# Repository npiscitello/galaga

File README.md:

# Sample Rate
If we run the system on the 8MHz internal clock and use 8-bit resolution PWM for the audio, we'll
have a sample rate of 8000000/256=31250 Hz. I used Audacity to prepare the audio files - project
rate of 31250, split into mono and delete one channel, then export the audio to unsigned 8 bit raw.

# FAT Driver
FatFS driver - see http://elm-chan.org/fsw/ff/00index_e.html (may take a while to load)

# KiCAD
Required libraries (may not be an all-inclusive list...):
 * custom library, bundled in this repo
 * Device
 * Connector
 * MCU_Microchip_ATmega
 * Amplifier_Audio
 * Regulator_Linear

# Random Number Generator
This project needs some way to decide which sound to play. The easy way out is
to just play one sound over and over, but I wanted more variety. I could rotate
over a list of sounds sequentially, but then I'd have to store which sound
played previously in the EEPROM and worry about wear leveling and all sorts of
mess, so I decided to just choose a random sound every time the chip starts up.
This also has the added bonus of not getting locked into a monotonous loop if
you want to play a few sounds in a row.

On the advice of a few threads over at AVRFreaks, I played around with using ADC
noise as an entropy source for a random number generator. I tried using the
internal temp sensor, but it ended up working much better to use ADC5, the pin
furthest from the GND pin. It probably didn't matter which pin I used (not that
I tested pin vs. pin performance), but it seemed like that was a free way to get
a little bit more noise on the line. That's a weird sentence to type, but noise
is desirable in this case!

The random number generator itself is dead simple - I read the two LSBs of the
ADC four times to fill an 8 bit unsigned int then just modulo that number with
the number of entries in my sound file array. That number is just an index into
that array and bam - random sound. See `code/main_code/sound_files.c` for the
implementation.

To test the randomness I cycled the chip 100 times and recorded the output of
the RNG. The histogram of the results is shown below - not the most even
distribution but certainly random enough for my purposes. This test also
doubled as a stability test, and I'm happy to report that it ran flawlessly,
with no errors or hiccups, all 100 times in a row!

![Histogram showing the results of 100 test runs of the RNG. The distribution is
satisfactorily random.](code/main_code/rng_histogram.png)

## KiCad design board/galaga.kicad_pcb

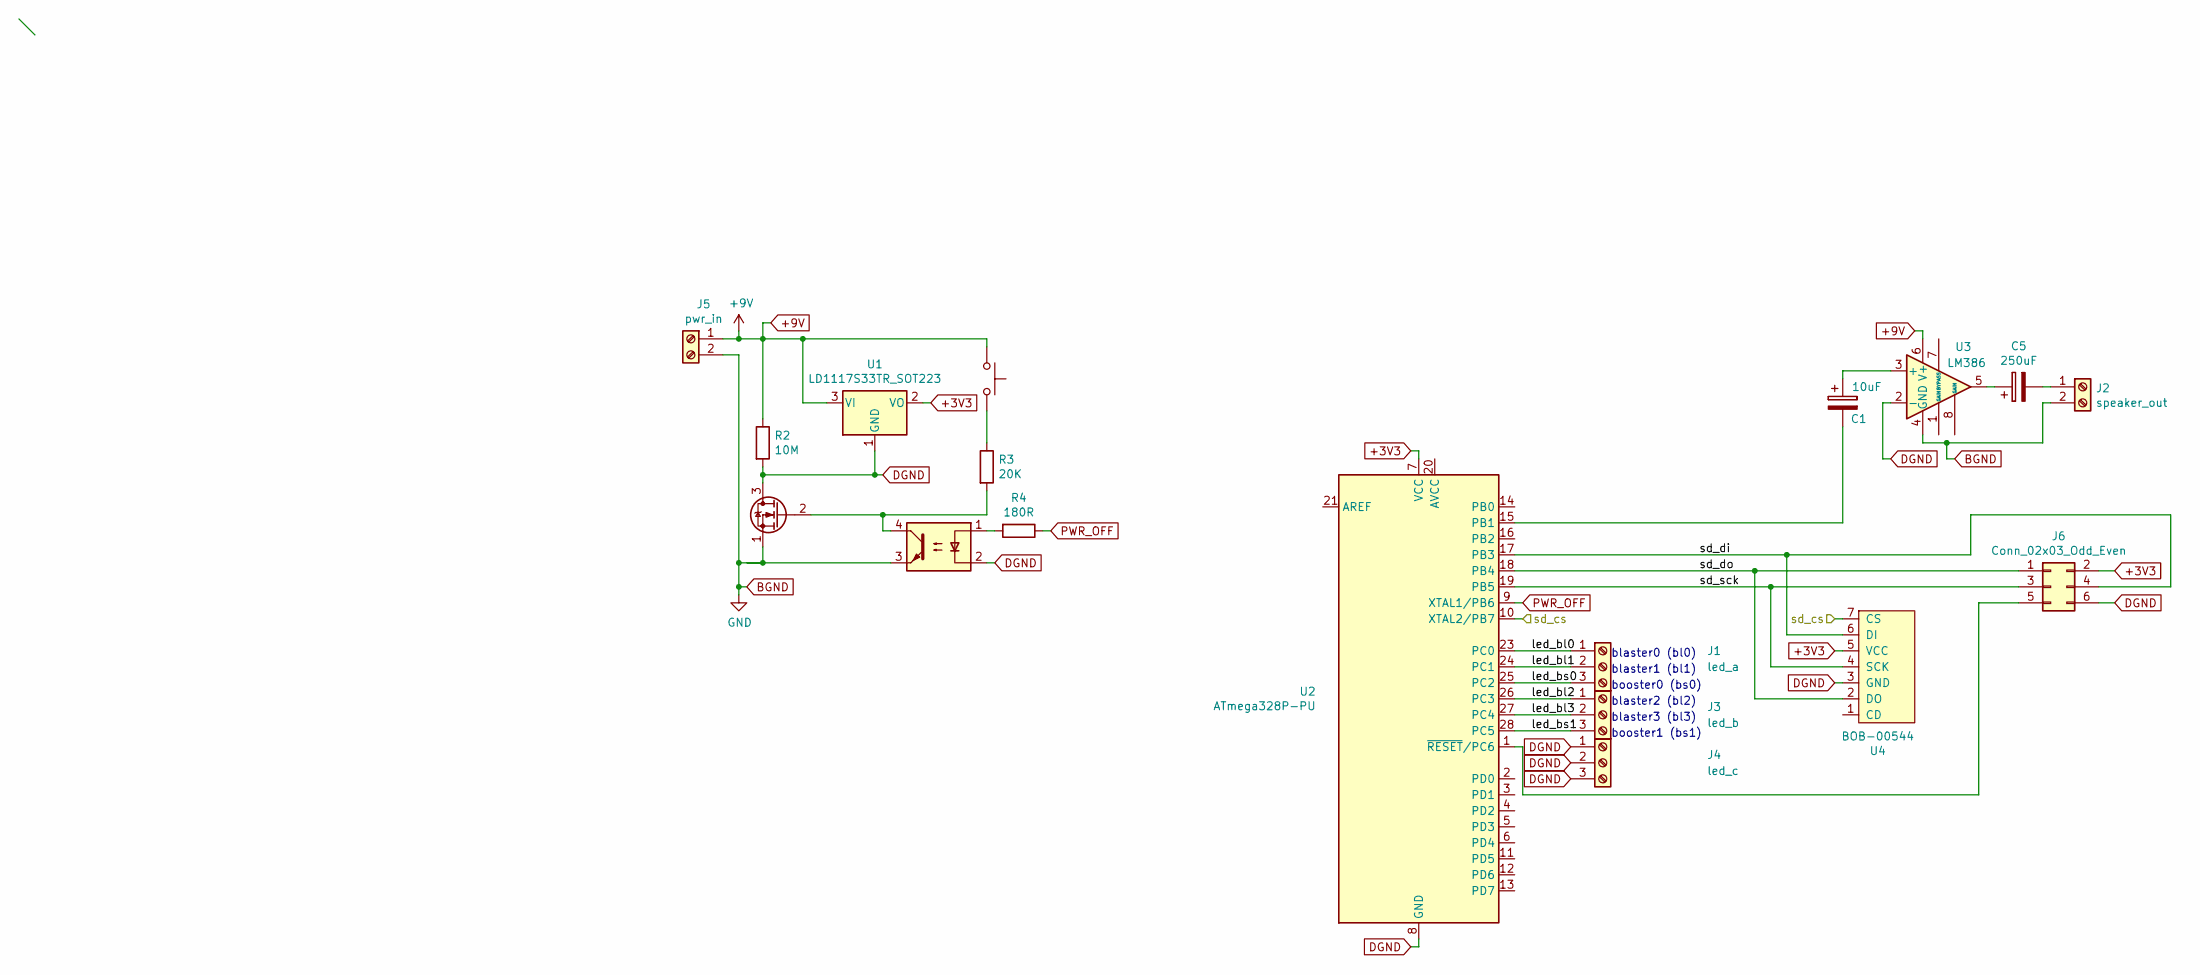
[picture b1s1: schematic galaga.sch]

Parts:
C1: 10uF; CP_Axial_L10.0mm_D6.0mm_P15.00mm_Horizontal
C5: 250uF; CP_Axial_L20.0mm_D10.0mm_P26.00mm_Horizontal
J1: led_a; TerminalBlock_TE_282834-3_1x03_P2.54mm_Horizontal
J2: speaker_out; TerminalBlock_TE_282834-2_1x02_P2.54mm_Horizontal
J3: led_b; TerminalBlock_TE_282834-3_1x03_P2.54mm_Horizontal
J4: led_c; TerminalBlock_TE_282834-3_1x03_P2.54mm_Horizontal
J5: pwr_in; TerminalBlock_TE_282834-2_1x02_P2.54mm_Horizontal
J6: Conn_02x03_Odd_Even; PinHeader_2x03_P2.54mm_Vertical
Q1: 2N7000; TO-220-3_Vertical
R2: 10M; R_Axial_DIN0207_L6.3mm_D2.5mm_P2.54mm_Vertical
R3: 20K; R_Axial_DIN0207_L6.3mm_D2.5mm_P2.54mm_Vertical
R4: 180R; R_Axial_DIN0207_L6.3mm_D2.5mm_P2.54mm_Vertical
SW1: SW_Push; TerminalBlock_TE_282834-2_1x02_P2.54mm_Horizontal
U1: LD1117S33TR_SOT223; TO-220-3_Vertical
U2: ATmega328P-PU; DIP-28_W7.62mm
U3: LM386; DIP-8_W7.62mm
U4: BOB-00544; PinHeader_1x07_P2.54mm_Vertical
U5: LTV-817M; DIP-4_W10.16mm

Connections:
+3V3: J6.2, U1.2 (VO), U2.7 (VCC), U4.5 (VCC)
+9V: J5.1, R2.1, SW1.1, U1.3 (VI), U3.6 (V+)
/led_bl0: J1.1, U2.23 (PC0)
/led_bl1: J1.2, U2.24 (PC1)
/led_bl2: J3.1, U2.26 (PC3)
/led_bl3: J3.2, U2.27 (PC4)
/led_bs0: J1.3, U2.25 (PC2)
/led_bs1: J3.3, U2.28 (PC5)
/sd_di: J6.4, U2.17 (PB3), U4.6 (DI)
/sd_do: J6.1, U2.18 (PB4), U4.2 (DO)
/sd_sck: J6.3, U2.19 (PB5), U4.4 (SCK)
BGND: J2.2, J5.2, Q1.1 (S), U3.4 (GND), U5.3
DGND: J4.1, J4.2, J4.3, J6.6, Q1.3 (D), R2.2, U1.1 (GND), U2.8 (GND), U2.22 (GND), U3.2 (-), U4.3 (GND), U5.2
unnamed: C1.1, U3.3 (+)
unnamed: C1.2, U2.15 (PB1)
unnamed: C5.1, U3.5
unnamed: C5.2, J2.1
unnamed: J6.5, U2.1 (~RESET~/PC6)
unnamed: Q1.2 (G), R3.2, U5.4
unnamed: R3.1, SW1.2
unnamed: R4.2, U5.1
PWR_OFF: R4.1, U2.9 (XTAL1/PB6)

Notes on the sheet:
blaster0 (bl0)
blaster1 (bl1)
blaster2 (bl2)
blaster3 (bl3)
booster0 (bs0)
booster1 (bs1)

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
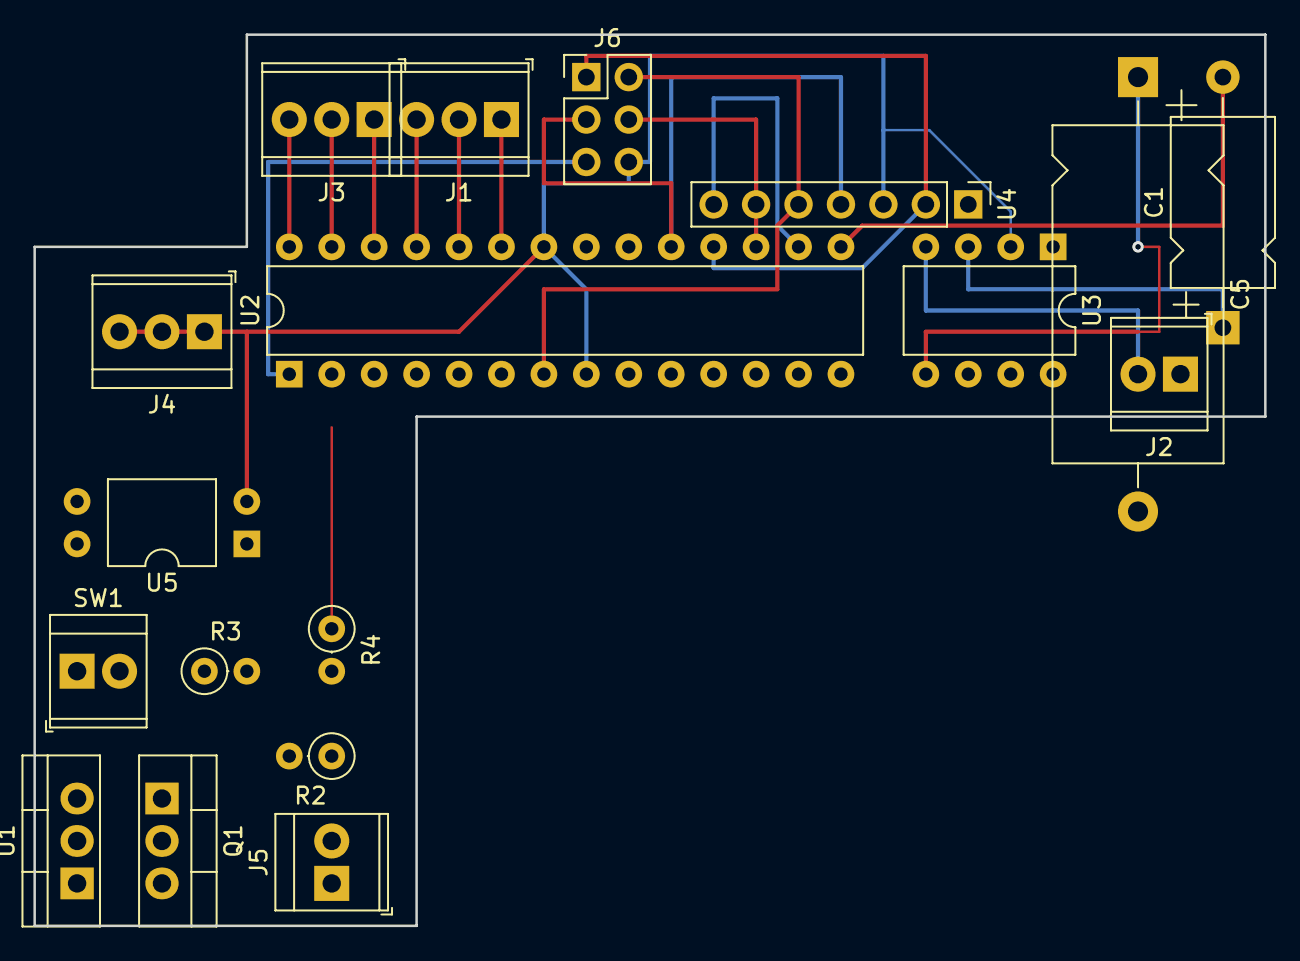
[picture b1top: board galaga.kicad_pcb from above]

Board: 2 copper layers, 73.7 x 53.3 mm, 18 parts (0 on the bottom side), 23 nets.

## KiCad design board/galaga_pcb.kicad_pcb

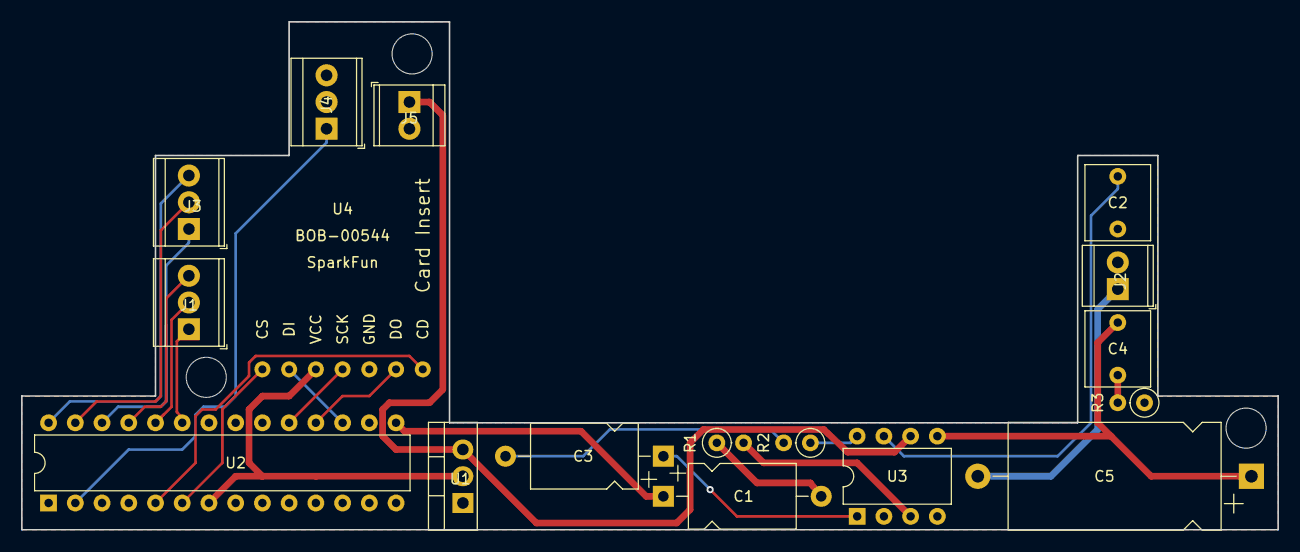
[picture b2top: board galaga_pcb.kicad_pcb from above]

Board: 2 copper layers, 119.4 x 48.3 mm, 17 parts (0 on the bottom side), 25 nets.

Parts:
C1, C3: 10uF; CP_Axial_L10.0mm_D6.0mm_P15.00mm_Horizontal
C2: 0.5uF; C_Rect_L7.0mm_W6.0mm_P5.00mm
C4: 0.05uF; C_Rect_L7.0mm_W6.0mm_P5.00mm
C5: 250uF; CP_Axial_L20.0mm_D10.0mm_P26.00mm_Horizontal
J1: led_a; TerminalBlock_TE_282834-3_1x03_P2.54mm_Horizontal
J2: speaker_out; TerminalBlock_TE_282834-2_1x02_P2.54mm_Horizontal
J3: led_b; TerminalBlock_TE_282834-3_1x03_P2.54mm_Horizontal
J4: led_c; TerminalBlock_TE_282834-3_1x03_P2.54mm_Horizontal
J5: pwr_in; TerminalBlock_TE_282834-2_1x02_P2.54mm_Horizontal
R1, R2: 10k (max); R_Axial_DIN0207_L6.3mm_D2.5mm_P2.54mm_Vertical
R3: 10; R_Axial_DIN0207_L6.3mm_D2.5mm_P2.54mm_Vertical
U1: LD1117S33TR_SOT223; TO-220-3_Vertical
U2: ATmega328P-PU; DIP-28_W7.62mm
U3: LM386; DIP-8_W7.62mm
U4: BOB-00544; bob-00544

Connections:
+3V3: U1.2, U2.7, U4.5
+9V: J5.1, U1.3, U3.6
/led_bl0: J1.1, U2.23
/led_bl1: J1.2, U2.24
/led_bl2: J3.1, U2.26
/led_bl3: J3.2, U2.27
/led_bs0: J1.3, U2.25
/led_bs1: J3.3, U2.28
/sd_cd: U2.5, U4.1
/sd_cs: U2.6, U4.7
/sd_di: U2.17, U4.6
/sd_do: U2.18, U4.2
/sd_sck: U2.19, U4.4
GND: C2.1, J2.2, J4.2, J4.3, J5.2, R3.1, U1.1, U2.8, U2.22, U3.2, U3.4, U4.3
unnamed: C1.1, U2.15
unnamed: C1.2, R1.1
unnamed: C2.2, U3.7
unnamed: C3.1, U3.1
unnamed: C3.2, R2.2
unnamed: C4.1, C5.1, U3.5
unnamed: C4.2, R3.2
unnamed: C5.2, J2.1
unnamed: J4.1, U2.2
unnamed: R1.2, U3.3
unnamed: R2.1, U3.8

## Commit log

2019-02-01 playing around with waveform generation
    We're gonna need to clock very, very fast - with 8 bit PCM at a 44100 Hz
    sample rate, we still need upwards of an 11 MHz system clock. With an
    8MHz clock, we can get a sample rate of 31250 tops. Maybe that's close
    enough for a 32000 Hz export? I'll try it and see...
2019-02-01 described approach to audio
2019-02-01 tried to get a waveform working...won't do it. need a scope.
2019-02-01 interrupt still doesn't seem to be firing...maybe try with a different timer?
2019-02-03 audio works, but not with the interrupt...
2019-02-03 RTFM. The interrupt vector macro is TIMER1_OVF_vect, not TIM1_OVF_vect.
2019-02-03 got an actual audio clip to play!
2019-02-06 cleanup
2019-02-13 found FAT driver
2019-02-17 stubbed out low-level driver funcs for fatfs
2019-03-13 took avr mmc sample; got it to compile, still need to tweak it for this project
2019-03-13 testing compiling functions in main
2019-03-18 added SPI clock macros
2019-07-06 extra #endif removed
2019-07-06 set up 10ms call for fatfs function
2019-07-06 tried to hack SD card together, getting a 'FR_NOT_READY' when calling 'f_mount' - the hardware implementation is definitely wrong.
2019-07-11 moved code in preparation to incorporate design files
2019-07-11 adding all the physical design files
2019-07-11 reorganized
2019-07-11 README update
2019-07-13 found an old version of ffs examples with (allegedly) working avr/sd comms
2019-07-13 timer was messed up (what's new?) but I think there's still a driver issue
2019-07-13 prepping to switch to petit ffs - we'll see if it works better
2019-07-13 moved stuff around. tried a small SD card and the full-sized FFS works! I'll keep messing with this to see if I can get it to work too...
2019-07-13 we don't need this heavy boi in here
2019-07-13 quick and dirty, doesn't work :(
2019-07-13 tweaking, but it's still not working
2019-07-13 it works now!!!
    Turns out, the guy who wrote this knows his own code better than me. Go
    figure. Changed the commands back and used the macros to wait for the
    SPI writes to finish and we're off to the races!
2019-07-13 ...and now I know you have to use ALL CAPS in the filename in the code
2019-07-22 used the fastest SPI clock and SD card mount is pretty quick. Might throw in an external crystal and bump the system clock to 16MHz if it turns out that's still too slow
2019-07-22 LED test file works!
2019-07-31 starting to work on double buffering stuff
2019-07-31 something's not quite working - going to rewind to make sure it used to work
2019-07-31 it works! It wasn't actually throwing an error, I just wrote my error handler wrong. No _BV macros!
2019-08-01 fixed loop: wasn't clearing the end of file flag
2019-09-03 got UART debug comms working!
2019-09-06 added self-power-off hardware to schematic
2019-09-06 added self-power-off function test. Plot twist, it works!
2019-09-06 rearranged components to support using perfboard instead of a manufactured PCB. I think it also uses the space better?
2019-09-06 started laying out board - doesn't have to be perfect (cuz it's perfboard) and there's some vertical room I'm playing with
2019-12-03 changed SD CS pin to PORTB7 for better board layout
2020-01-06 added self power-off test code
2020-01-07 revamped power and amp circuits, going back to breadboard testing before circuit construction
2020-01-07 seems like SPI isn't working as expected - SPIF flag doesn't seem to get set
2020-01-07 can't find the SPI issue - gonna do a minimum test case
2020-01-07 spif still hanging
2020-01-07 fixed! needed to make the SS pin output
    Floating input was knocking the chip out of master mode.
    https://www.avrfreaks.net/forum/spif-flag-strange-behavior
2020-01-07 fixed EOF and SD card op logic
2020-01-10 finished the board, worked first shot!
2020-01-11 let button come up into cockpit more
2020-01-11 started stubbing out filename management for the main code
2020-01-21 untested ADC 'random' number generator
2020-01-21 The package is coming together!
    Random doesn't really work, it seems to alternate between two numbers,
    but it might be a hardware setup issue. Still, it makes noise!
2020-01-30 fixed poweroff - one line!!!!! -_-
    Random is still having trouble - it seems like it's sorta getting kinda
    random stuff, but it's a little too consistent for my taste. I'll have
    to do some testing.
2020-01-30 adding sounds to repo cuz they're kinda important to the project...
2020-01-30 Hopefully fixed no power off bug
    I moved the power latch later in the setup sequence - my theory is that
    the chip was browning out when the power pin brought the power down,
    jumping to the reset vector (without fully resetting), and running main
    again. Since the (nearly) first instruction in main was to latch the
    power on, the power stayed on. Moving the latch instruction to right
    before the first buffer fill should still be quick enough that a human
2020-01-30 testing random function
    It's working - the reason it seemed like it was locking up was that one
    of my filenames was too long; I fixed that and it hits every time now.
    It's still a little too 'consistent' for my liking, but humans aren't
    too good at true randomness so <shrug>. I'll search around for other
    ways to generate 'randomness' on an AVR, but if I need to stick with
    this, I'll just artificially weight the sounds I like better by putting
2020-02-10 RNG tweaked, tested, and working!
    All that's really left now is to make the lights flash and assemble
    everything. Making the while loop break at the end of file flag instad
    of polling seems to have fixed the no-power-off issue - it powered off
    perfectly 100 times in a row!
2020-02-29 led flashing demo implemented, broke rng...
2020-02-29 implemented programmable LED animation, fixed rng
2020-02-29 added led bootup, added a nicer animation
2020-03-01 added stand to CAD model
2020-03-21 project finished - cleanup commit
